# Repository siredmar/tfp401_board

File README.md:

tfp401_board
============

Hard- and Software for TFP401 Board to connect with 40 Pin RGB LCDs

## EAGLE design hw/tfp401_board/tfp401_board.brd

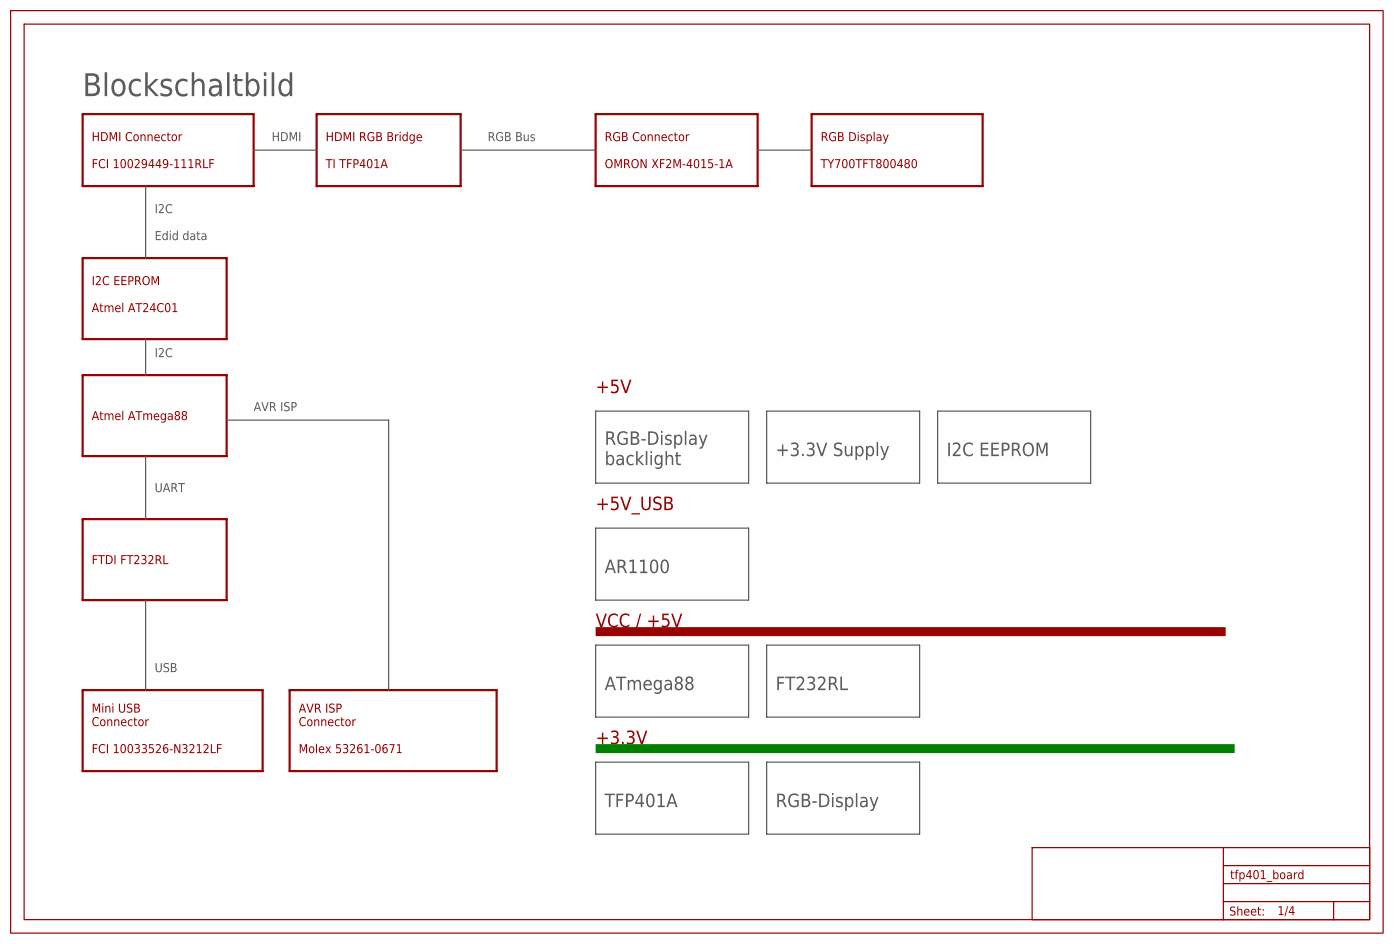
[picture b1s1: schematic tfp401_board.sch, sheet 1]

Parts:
U$15: FRAME_A3_LANDSCAPE; FRAME

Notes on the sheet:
HDMI Connector FCI 10029449-111RLF
RGB Display TY700TFT800480
Mini USB Connector FCI 10033526-N3212LF
AVR ISP Connector Molex 53261-0671
RGB Connector OMRON XF2M-4015-1A
HDMI RGB Bridge TI TFP401A
I2C EEPROM Atmel AT24C01
Atmel ATmega88
Edid data
RGB Bus
I2C
USB
AVR ISP
HDMI
Blockschaltbild
+3.3V
VCC / +5V
ATmega88
I2C EEPROM
FT232RL
TFP401A
FTDI FT232RL
UART
RGB-Display backlight
RGB-Display
+5V
AR1100
+5V_USB
+3.3V Supply

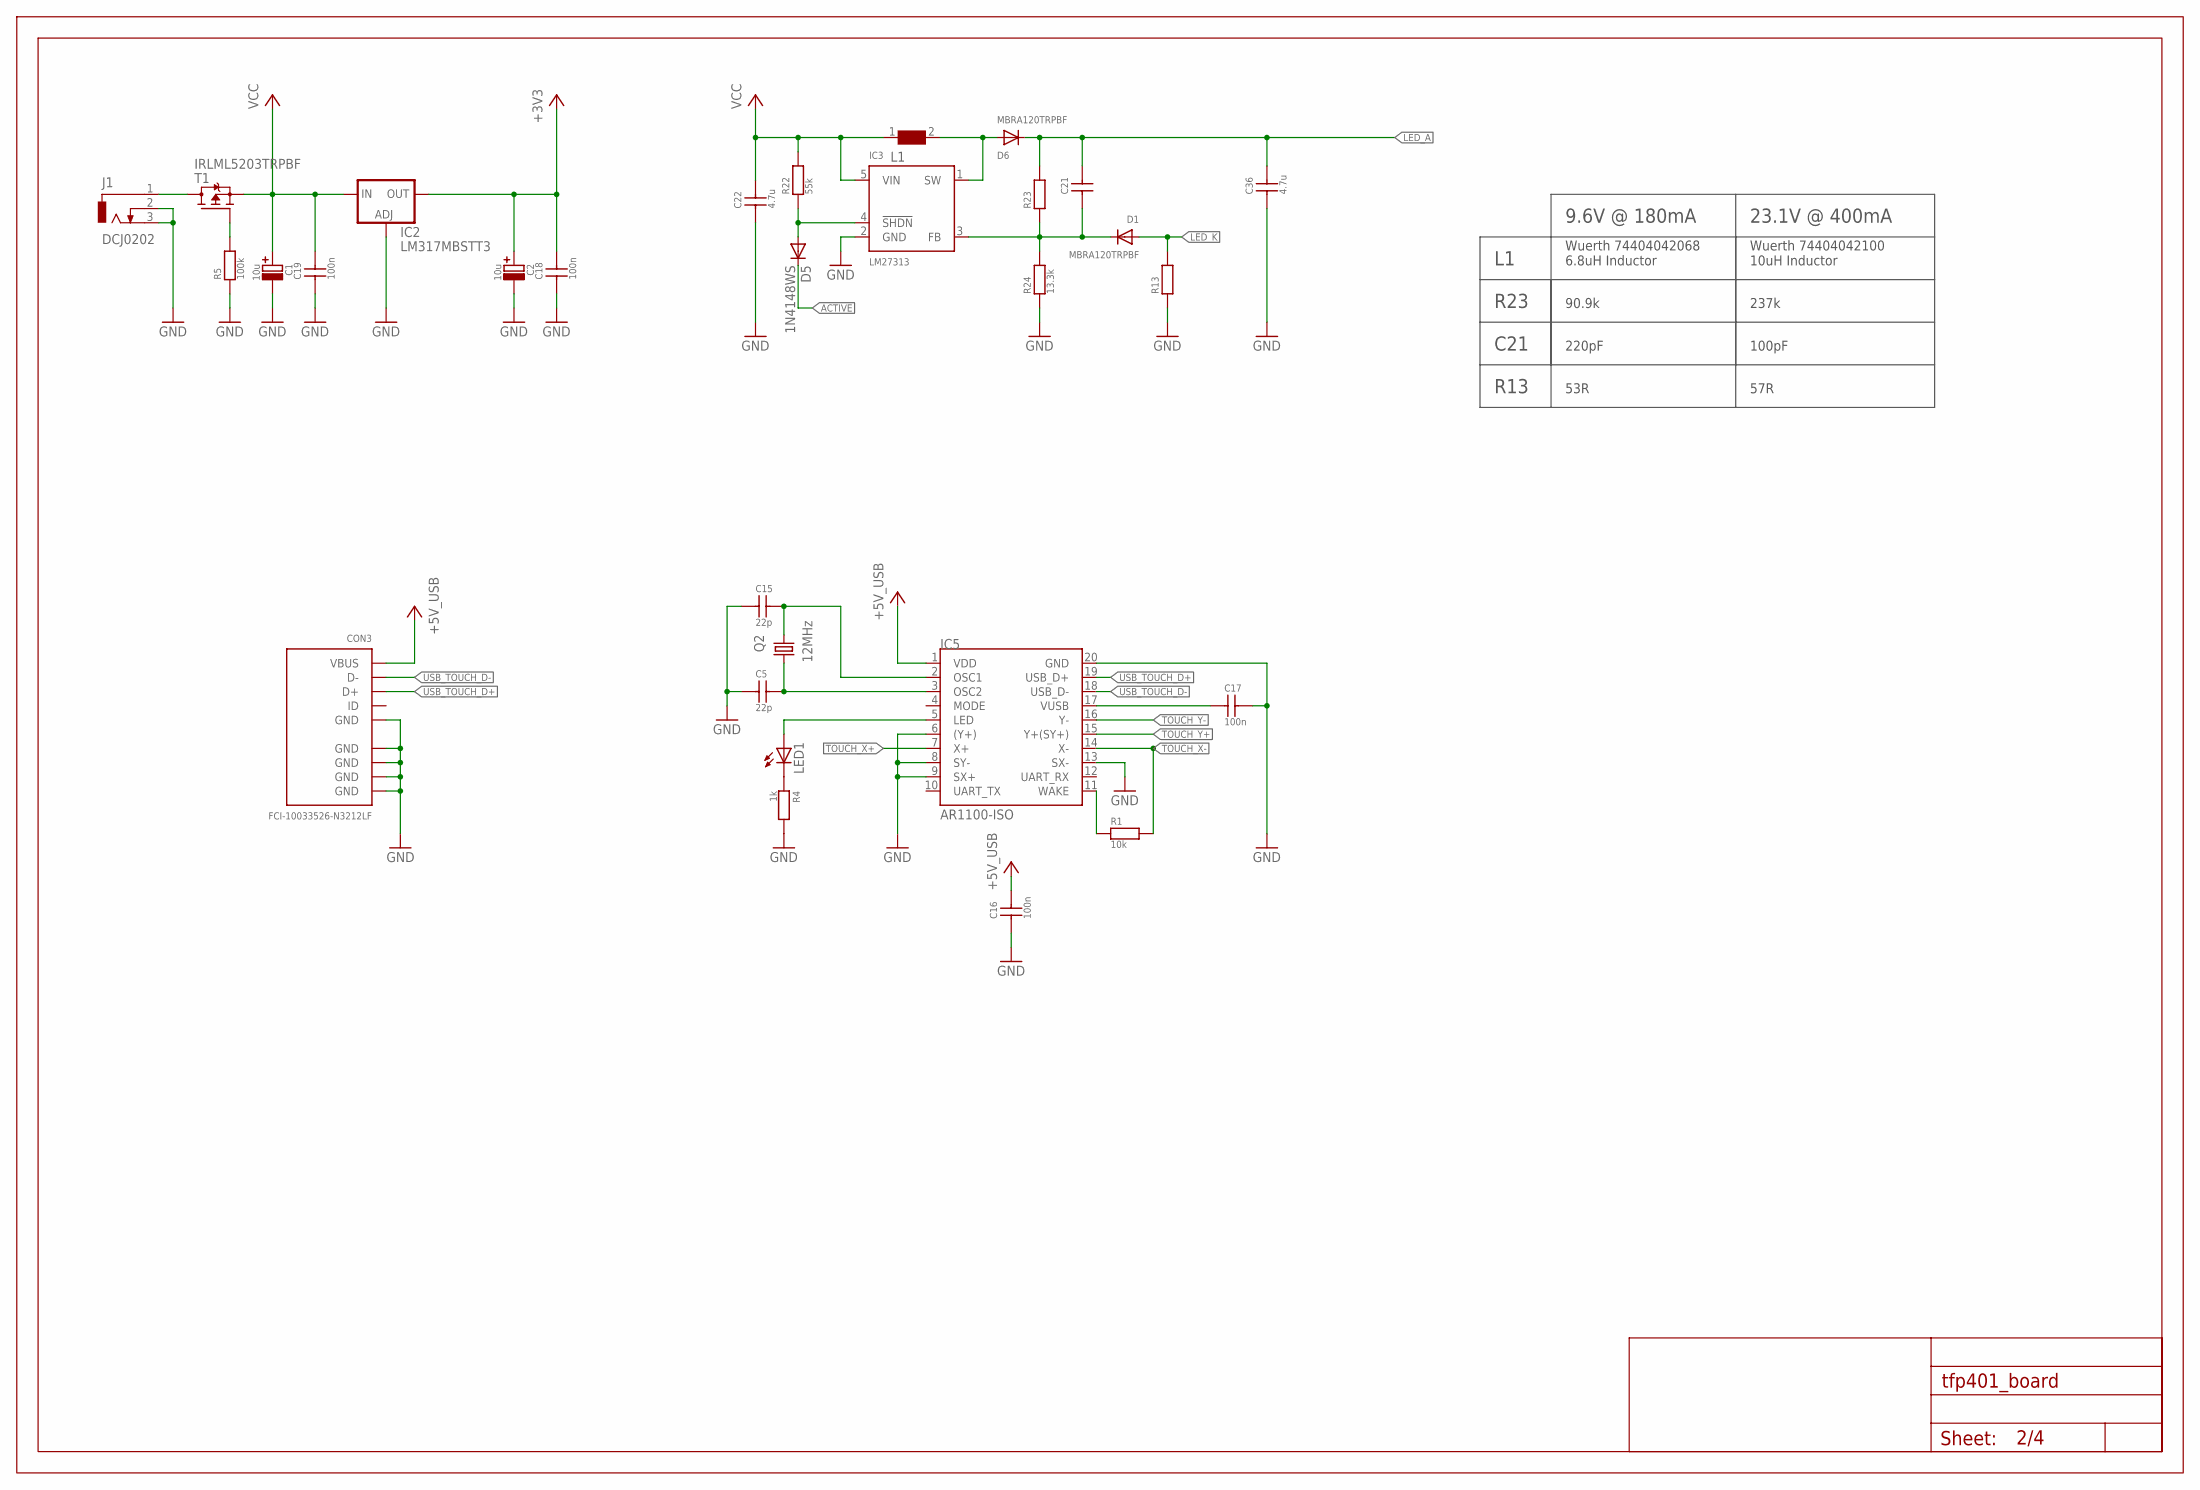
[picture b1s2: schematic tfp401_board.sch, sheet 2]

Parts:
C1, C2: 10u; C_POL_4X4MM
C5, C15: 22p; C0603
C16, C17, C18, C19: 100n; C0603
C21: C_SMD0603; C0603
C22, C36: 4.7u; C1206
CON3: FCI-10033526-N3212LF
D1, D6: MBRA120TRPBF; SMADIODE
D5: 1N4148WS; SOD323-W
IC2: LM317MBSTT3; SOT223
IC3: LM27313; SOT23-5
IC5: AR1100-ISO; SOIC20
J1: DCJ0202
L1: WE-LQS_4018
LED1: LEDCHIP-LED0805; CHIP-LED0805
Q2: 12MHz; HC49/USSM
R1: 10k; R0603
R4: 1k; R0603
R5: 100k; R0603
R13: R2512
R22: 55k; R0603
R23: R0603
R24: 13.3k; R0603
T1: IRLML5203TRPBF; SOT23
U$2: FRAME_A3_LANDSCAPE; FRAME

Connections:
+3V3: C2.+, C18.2, IC2.4 (OUT); also elsewhere on the board
+5V_USB: C16.2, CON3.1 (VBUS), IC5.1 (VDD)
ACTIVE: D5.C; also elsewhere on the board
GND: C1.-, C2.-, C5.1, C15.1, C16.1, C17.2, C18.1, C19.1, C22.1, C36.1, CON3.5 (GND), CON3.GND@1 (GND), CON3.GND@2 (GND), CON3.GND@3 (GND), CON3.GND@4 (GND), IC2.1 (ADJ), IC3.2 (GND), IC5.6 ((Y+)), IC5.8 (SY-), IC5.9 (SX+), IC5.13 (SX-), IC5.20 (GND), J1.2, J1.3, R4.2, R5.1, R13.1, R24.1; also elsewhere on the board
LED_A: C21.2, C36.2, D6.C, R23.2; also elsewhere on the board
LED_K: D1.A, R13.2; also elsewhere on the board
unnamed: R5.2, T1.1 (G)
unnamed: IC5.11 (WAKE), R1.1
unnamed: C17.1, IC5.17 (VUSB)
unnamed: LED1.C, R4.1
unnamed: C15.2, IC5.2 (OSC1), Q2.1
unnamed: J1.1, T1.3 (D)
unnamed: C5.2, IC5.3 (OSC2), Q2.2
unnamed: D6.A, IC3.1 (SW), L1.2
unnamed: D5.A, IC3.4 (!SHDN), R22.1
unnamed: IC5.5 (LED), LED1.A
unnamed: C21.1, D1.C, IC3.3 (FB), R23.1, R24.2
TOUCH_X+: IC5.7 (X+); also elsewhere on the board
TOUCH_X-: IC5.14 (X-), R1.2; also elsewhere on the board
TOUCH_Y+: IC5.15 (Y+(SY+)); also elsewhere on the board
TOUCH_Y-: IC5.16 (Y-); also elsewhere on the board
USB_TOUCH_D+: CON3.3 (D+), IC5.19 (USB_D+)
USB_TOUCH_D-: CON3.2 (D-), IC5.18 (USB_D-)
VCC: C1.+, C19.2, C22.2, IC2.3 (IN), IC3.5 (VIN), L1.1, R22.2, T1.2 (S); also elsewhere on the board

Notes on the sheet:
9.6V @ 180mA
23.1V @ 400mA
R23
Wuerth 74404042068 6.8uH Inductor
Wuerth 74404042100 10uH Inductor
C21
90.9k
237k
100pF
220pF
R13
57R
53R

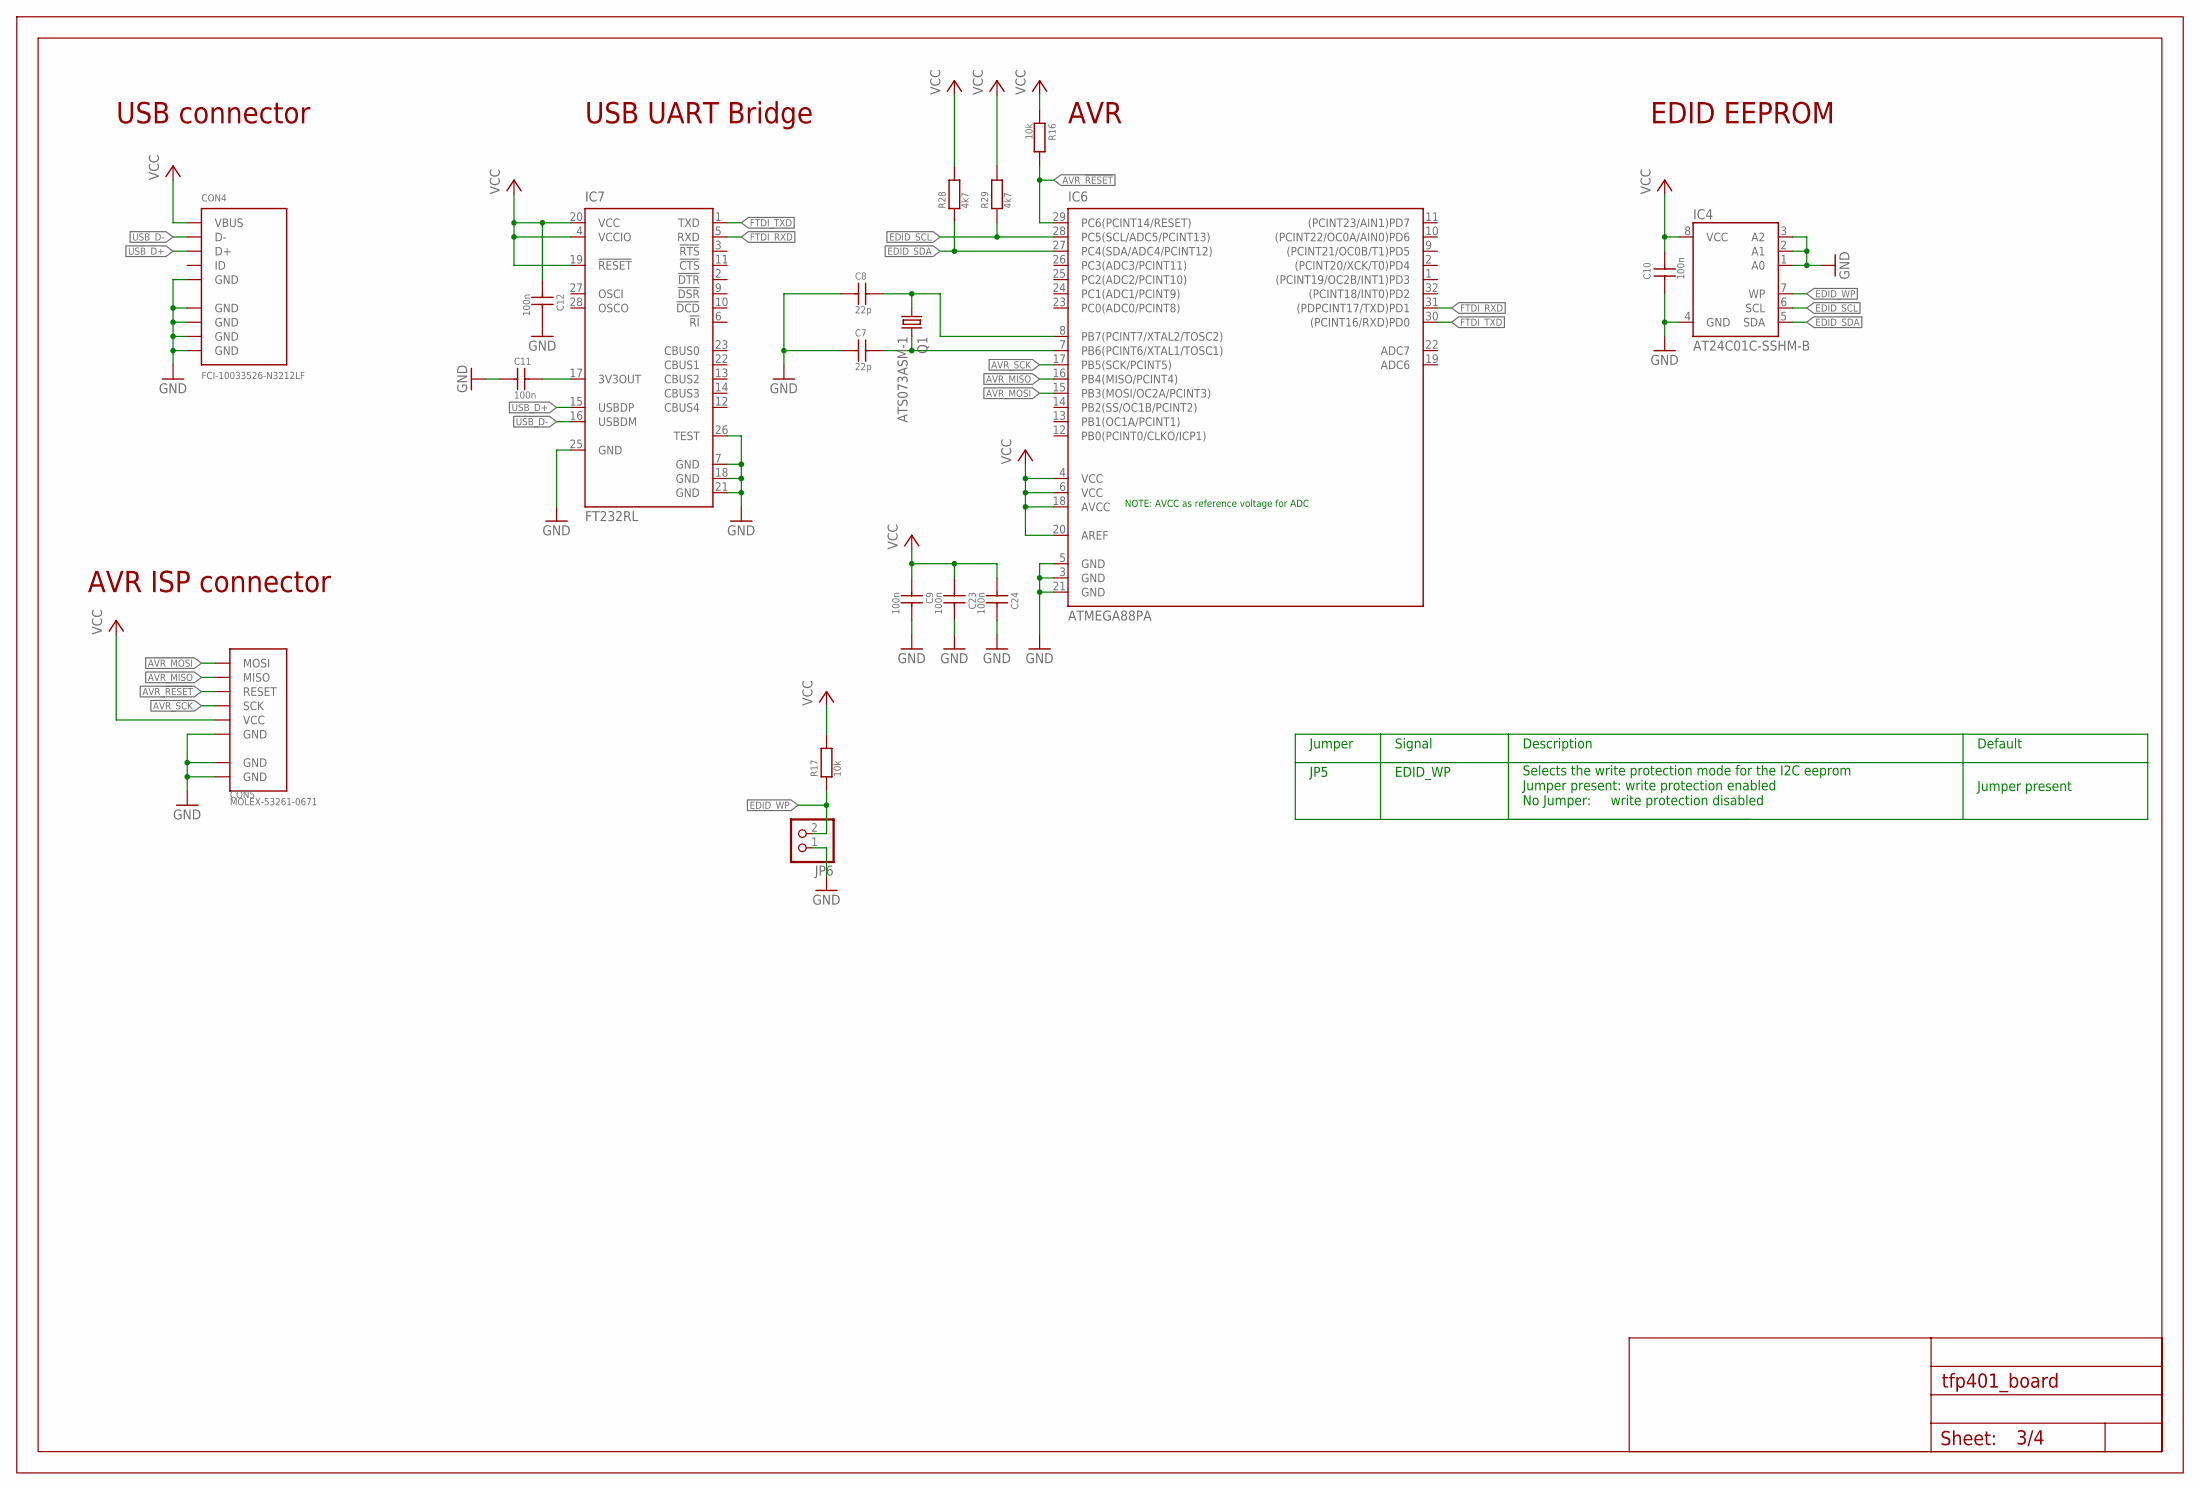
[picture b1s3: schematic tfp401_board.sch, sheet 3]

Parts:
C7, C8: 22p; C0603
C9, C10, C11, C12, C23, C24: 100n; C0603
CON4: FCI-10033526-N3212LF
CON5: MOLEX-53261-0671
IC4: AT24C01C-SSHM-B; SOIC8
IC6: ATMEGA88PA; TQFP32
IC7: FT232RL; SSOP28
JP6: PINHD-1X02_2.54-SMD-90°; 1X02SMD/90
Q1: ATS073ASM-1; HC49/USSM
R16, R17: 10k; R0603
R28, R29: 4k7; R0603
U$4: FRAME_A3_LANDSCAPE; FRAME

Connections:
AVR_!RESET: CON5.3 (RESET), IC6.29 (PC6(PCINT14/RESET)), R16.2
AVR_MISO: CON5.2 (MISO), IC6.16 (PB4(MISO/PCINT4))
AVR_MOSI: CON5.1 (MOSI), IC6.15 (PB3(MOSI/OC2A/PCINT3))
AVR_SCK: CON5.4 (SCK), IC6.17 (PB5(SCK/PCINT5))
AVR_XTAL1: C7.2, IC6.7 (PB6(PCINT6/XTAL1/TOSC1)), Q1.2
AVR_XTAL2: C8.2, IC6.8 (PB7(PCINT7/XTAL2/TOSC2)), Q1.1
EDID_SCL: IC4.6 (SCL), IC6.28 (PC5(SCL/ADC5/PCINT13)), R29.1; also elsewhere on the board
EDID_SDA: IC4.5 (SDA), IC6.27 (PC4(SDA/ADC4/PCINT12)), R28.1; also elsewhere on the board
EDID_WP: IC4.7 (WP), JP6.2, R17.1
FTDI_3V3OUT: C11.2, IC7.17 (3V3OUT)
FTDI_RXD: IC6.31 ((PDPCINT17/TXD)PD1), IC7.5 (RXD)
FTDI_TXD: IC6.30 ((PCINT16/RXD)PD0), IC7.1 (TXD)
GND: C7.1, C8.1, C9.2, C10.1, C11.1, C12.2, C23.2, C24.2, CON4.5 (GND), CON4.GND@1 (GND), CON4.GND@2 (GND), CON4.GND@3 (GND), CON4.GND@4 (GND), CON5.6 (GND), CON5.GND@1 (GND), CON5.GND@2 (GND), IC4.1 (A0), IC4.2 (A1), IC4.3 (A2), IC4.4 (GND), IC6.3 (GND), IC6.5 (GND), IC6.21 (GND), IC7.7 (GND), IC7.18 (GND), IC7.21 (GND), IC7.25 (GND), IC7.26 (TEST), JP6.1; also elsewhere on the board
USB_D+: CON4.3 (D+), IC7.15 (USBDP)
USB_D-: CON4.2 (D-), IC7.16 (USBDM)
VCC: C9.1, C10.2, C12.1, C23.1, C24.1, CON4.1 (VBUS), CON5.5 (VCC), IC4.8 (VCC), IC6.4 (VCC), IC6.6 (VCC), IC6.18 (AVCC), IC6.20 (AREF), IC7.4 (VCCIO), IC7.19 (!RESET), IC7.20 (VCC), R16.1, R17.2, R28.2, R29.2; also elsewhere on the board

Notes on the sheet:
NOTE: AVCC as reference voltage for ADC
JP5
Jumper
Description
Signal
EDID_WP
Selects the write protection mode for the I2C eeprom Jumper present: write protection enabled No Jumper: write protection disabled
Default
Jumper present
EDID EEPROM
AVR
USB UART Bridge
AVR ISP connector
USB connector

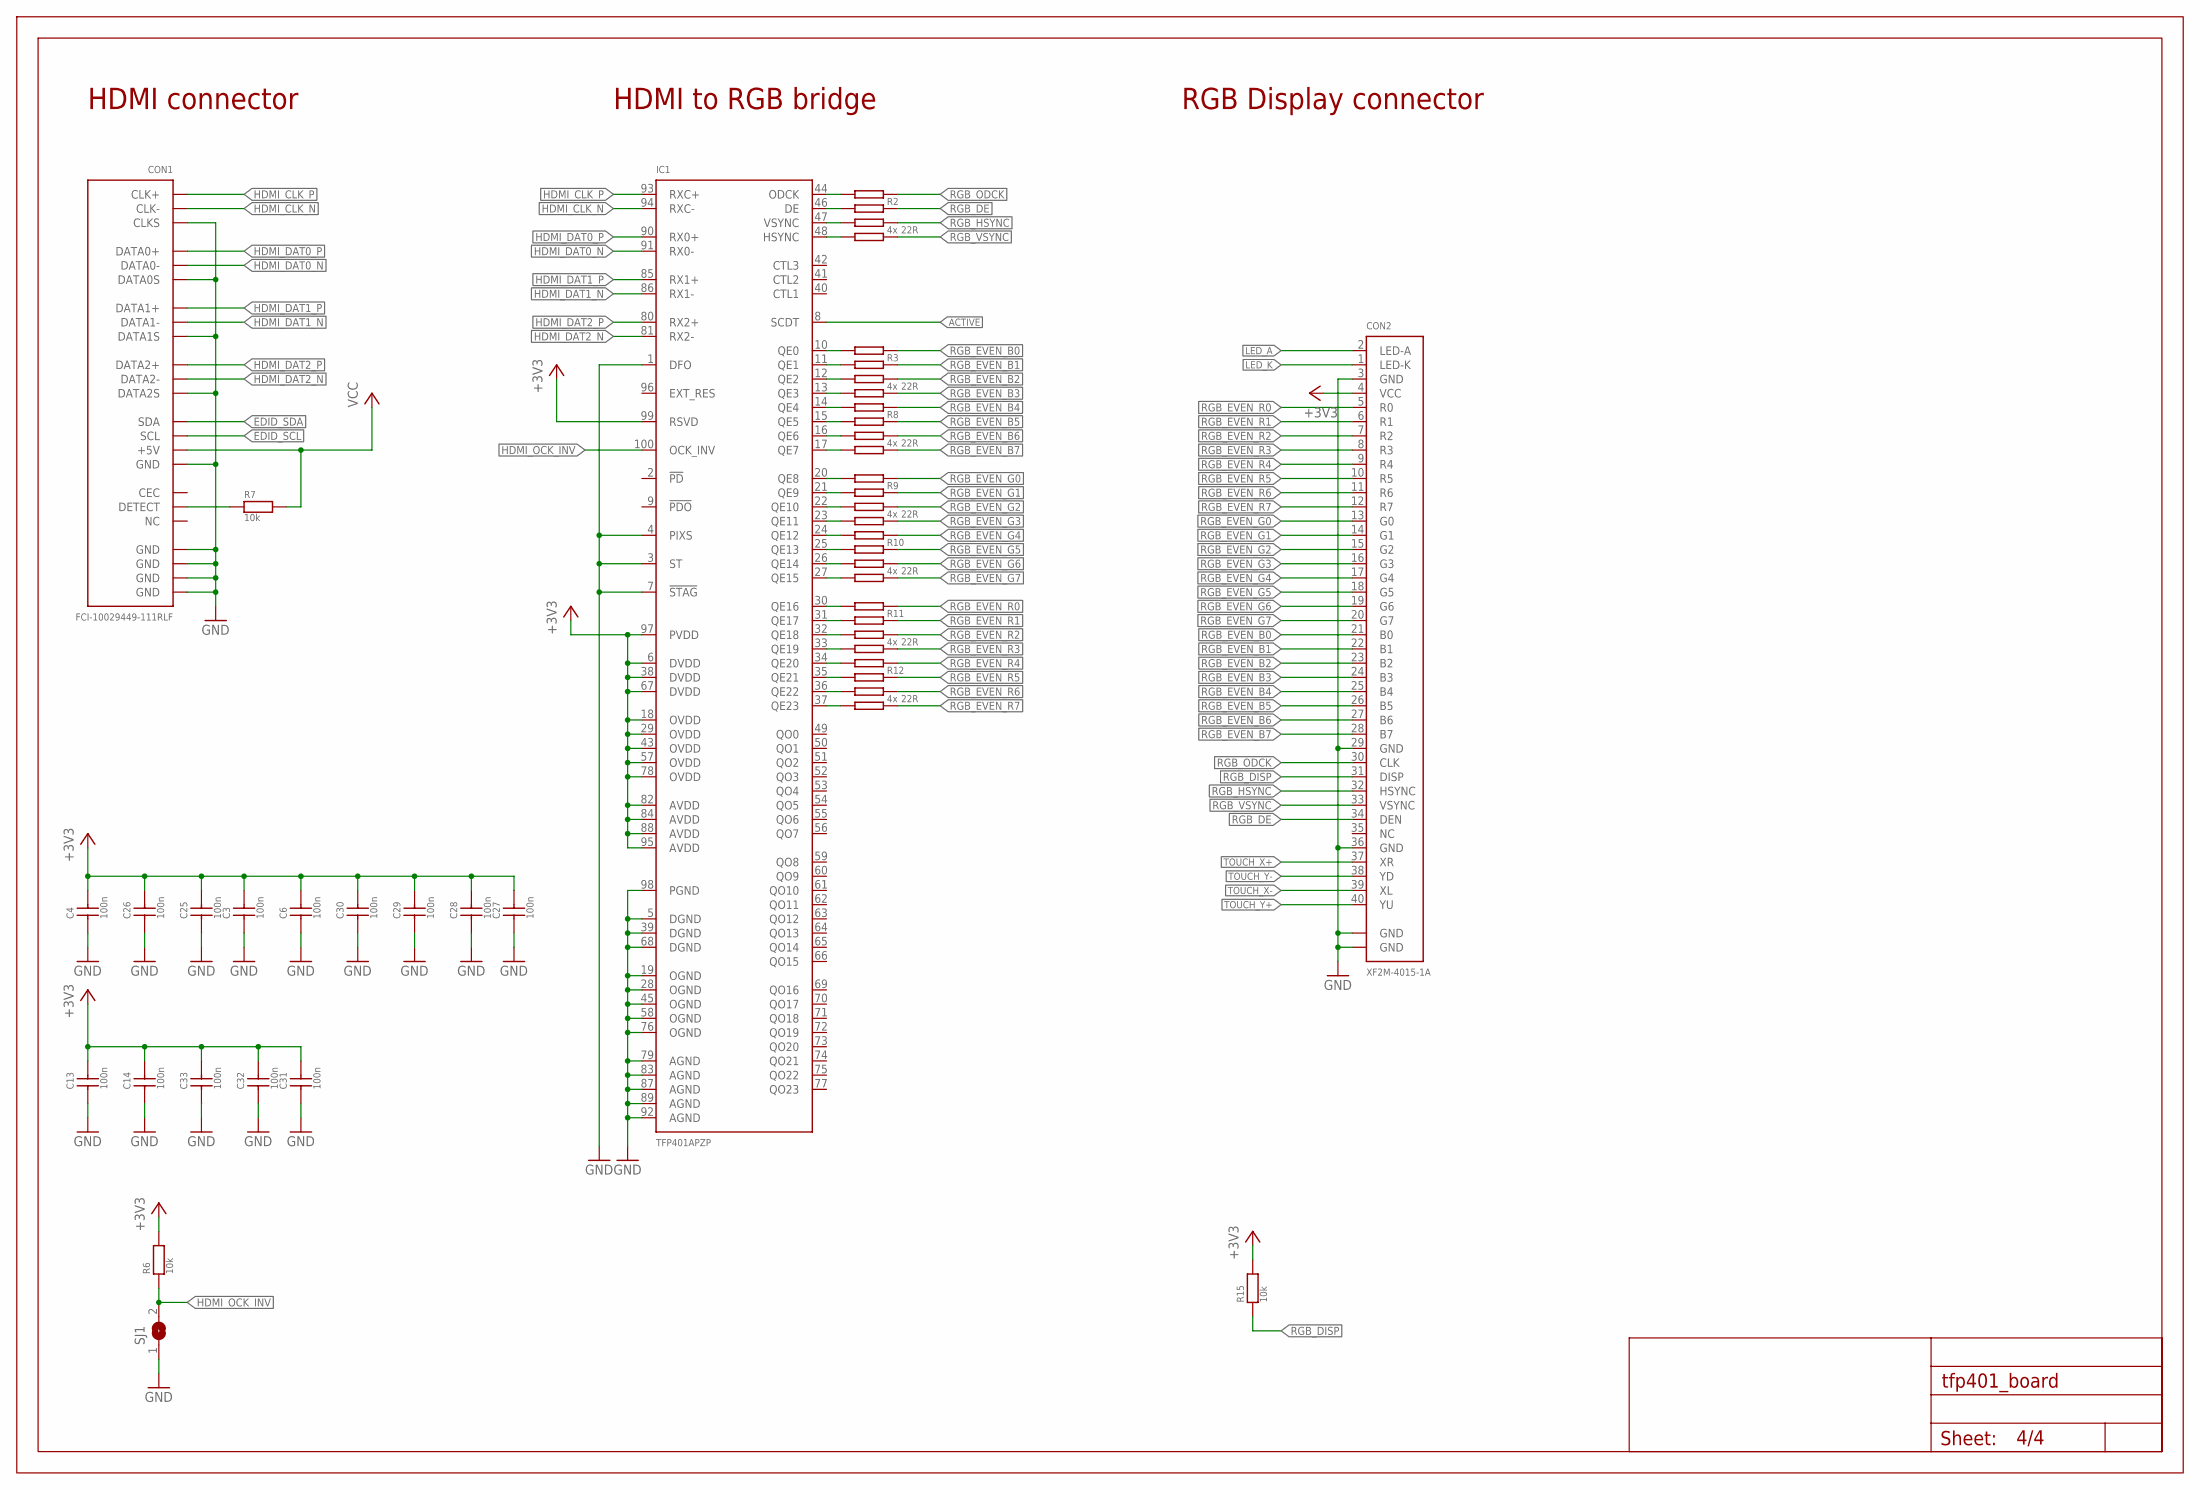
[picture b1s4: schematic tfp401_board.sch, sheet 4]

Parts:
C3, C4, C6, C13, C14, C25, C26, C27, C28, C29, C30, C31, C32, C33: 100n; C0603
CON1: FCI-10029449-111RLF
CON2: XF2M-4015-1A
IC1: TFP401APZP; HTQFP-100
R2, R3, R8, R9, R10, R11, R12: 22R; R-ARRAY-4X0603
R6, R7, R15: 10k; R0603
SJ1: SJ
U$1: FRAME_A3_LANDSCAPE; FRAME

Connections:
+3V3: C3.2, C4.2, C6.2, C13.2, C14.2, C25.2, C26.2, C27.2, C28.2, C29.2, C30.2, C31.2, C32.2, C33.2, CON2.4 (VCC), IC1.6 (DVDD), IC1.18 (OVDD), IC1.29 (OVDD), IC1.38 (DVDD), IC1.43 (OVDD), IC1.57 (OVDD), IC1.67 (DVDD), IC1.78 (OVDD), IC1.82 (AVDD), IC1.84 (AVDD), IC1.88 (AVDD), IC1.95 (AVDD), IC1.97 (PVDD), IC1.99 (RSVD), R6.2, R15.2; also elsewhere on the board
ACTIVE: IC1.8 (SCDT); also elsewhere on the board
EDID_SCL: CON1.15 (SCL); also elsewhere on the board
EDID_SDA: CON1.16 (SDA); also elsewhere on the board
GND: C3.1, C4.1, C6.1, C13.1, C14.1, C25.1, C26.1, C27.1, C28.1, C29.1, C30.1, C31.1, C32.1, C33.1, CON1.2 (DATA2S), CON1.5 (DATA1S), CON1.8 (DATA0S), CON1.11 (CLKS), CON1.17 (GND), CON1.GND@1 (GND), CON1.GND@2 (GND), CON1.GND@3 (GND), CON1.GND@4 (GND), CON2.3 (GND), CON2.29 (GND), CON2.36 (GND), CON2.GND@1 (GND), CON2.GND@2 (GND), IC1.1 (DFO), IC1.3 (ST), IC1.4 (PIXS), IC1.5 (DGND), IC1.7 (!STAG), IC1.19 (OGND), IC1.28 (OGND), IC1.39 (DGND), IC1.45 (OGND), IC1.58 (OGND), IC1.68 (DGND), IC1.76 (OGND), IC1.79 (AGND), IC1.83 (AGND), IC1.87 (AGND), IC1.89 (AGND), IC1.92 (AGND), IC1.98 (PGND), SJ1.1; also elsewhere on the board
HDMI_CLK_N: CON1.12 (CLK-), IC1.94 (RXC-)
HDMI_CLK_P: CON1.10 (CLK+), IC1.93 (RXC+)
HDMI_DAT0_N: CON1.9 (DATA0-), IC1.91 (RX0-)
HDMI_DAT0_P: CON1.7 (DATA0+), IC1.90 (RX0+)
HDMI_DAT1_N: CON1.6 (DATA1-), IC1.86 (RX1-)
HDMI_DAT1_P: CON1.4 (DATA1+), IC1.85 (RX1+)
HDMI_DAT2_N: CON1.3 (DATA2-), IC1.81 (RX2-)
HDMI_DAT2_P: CON1.1 (DATA2+), IC1.80 (RX2+)
HDMI_OCK_INV: IC1.100 (OCK_INV), R6.1, SJ1.2
INT_RGB_DE: IC1.46 (DE), R2.3M
INT_RGB_EVEN_B0: IC1.10 (QE0), R3.4M
INT_RGB_EVEN_B1: IC1.11 (QE1), R3.3M
INT_RGB_EVEN_B2: IC1.12 (QE2), R3.2M
INT_RGB_EVEN_B3: IC1.13 (QE3), R3.1M
INT_RGB_EVEN_B4: IC1.14 (QE4), R8.4M
INT_RGB_EVEN_B5: IC1.15 (QE5), R8.3M
INT_RGB_EVEN_B6: IC1.16 (QE6), R8.2M
INT_RGB_EVEN_B7: IC1.17 (QE7), R8.1M
INT_RGB_EVEN_G0: IC1.20 (QE8), R9.4M
INT_RGB_EVEN_G1: IC1.21 (QE9), R9.3M
INT_RGB_EVEN_G2: IC1.22 (QE10), R9.2M
INT_RGB_EVEN_G3: IC1.23 (QE11), R9.1M
INT_RGB_EVEN_G4: IC1.24 (QE12), R10.4M
INT_RGB_EVEN_G5: IC1.25 (QE13), R10.3M
INT_RGB_EVEN_G6: IC1.26 (QE14), R10.2M
INT_RGB_EVEN_G7: IC1.27 (QE15), R10.1M
INT_RGB_EVEN_R0: IC1.30 (QE16), R11.4M
INT_RGB_EVEN_R1: IC1.31 (QE17), R11.3M
INT_RGB_EVEN_R2: IC1.32 (QE18), R11.2M
INT_RGB_EVEN_R3: IC1.33 (QE19), R11.1M
INT_RGB_EVEN_R4: IC1.34 (QE20), R12.4M
INT_RGB_EVEN_R5: IC1.35 (QE21), R12.3M
INT_RGB_EVEN_R6: IC1.36 (QE22), R12.2M
INT_RGB_EVEN_R7: IC1.37 (QE23), R12.1M
INT_RGB_HSYNC: IC1.47 (VSYNC), R2.2M
INT_RGB_ODCK: IC1.44 (ODCK), R2.4M
INT_RGB_VSYNC: IC1.48 (HSYNC), R2.1M
LED_A: CON2.2 (LED-A); also elsewhere on the board
LED_K: CON2.1 (LED-K); also elsewhere on the board
unnamed: CON1.19 (DETECT), R7.1
RGB_DE: CON2.34 (DEN), R2.3P
RGB_DISP: CON2.31 (DISP), R15.1
RGB_EVEN_B0: CON2.21 (B0), R3.4P
RGB_EVEN_B1: CON2.22 (B1), R3.3P
RGB_EVEN_B2: CON2.23 (B2), R3.2P
RGB_EVEN_B3: CON2.24 (B3), R3.1P
RGB_EVEN_B4: CON2.25 (B4), R8.4P
RGB_EVEN_B5: CON2.26 (B5), R8.3P
RGB_EVEN_B6: CON2.27 (B6), R8.2P
RGB_EVEN_B7: CON2.28 (B7), R8.1P
RGB_EVEN_G0: CON2.13 (G0), R9.4P
RGB_EVEN_G1: CON2.14 (G1), R9.3P
RGB_EVEN_G2: CON2.15 (G2), R9.2P
RGB_EVEN_G3: CON2.16 (G3), R9.1P
RGB_EVEN_G4: CON2.17 (G4), R10.4P
RGB_EVEN_G5: CON2.18 (G5), R10.3P
RGB_EVEN_G6: CON2.19 (G6), R10.2P
RGB_EVEN_G7: CON2.20 (G7), R10.1P
RGB_EVEN_R0: CON2.5 (R0), R11.4P
RGB_EVEN_R1: CON2.6 (R1), R11.3P
RGB_EVEN_R2: CON2.7 (R2), R11.2P
RGB_EVEN_R3: CON2.8 (R3), R11.1P
RGB_EVEN_R4: CON2.9 (R4), R12.4P
RGB_EVEN_R5: CON2.10 (R5), R12.3P
RGB_EVEN_R6: CON2.11 (R6), R12.2P
RGB_EVEN_R7: CON2.12 (R7), R12.1P
RGB_HSYNC: CON2.32 (HSYNC), R2.2P
RGB_ODCK: CON2.30 (CLK), R2.4P
RGB_VSYNC: CON2.33 (VSYNC), R2.1P
TOUCH_X+: CON2.37 (XR); also elsewhere on the board
TOUCH_X-: CON2.39 (XL); also elsewhere on the board
TOUCH_Y+: CON2.40 (YU); also elsewhere on the board
TOUCH_Y-: CON2.38 (YD); also elsewhere on the board
VCC: CON1.18 (+5V), R7.2; also elsewhere on the board

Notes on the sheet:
HDMI connector
HDMI to RGB bridge
RGB Display connector

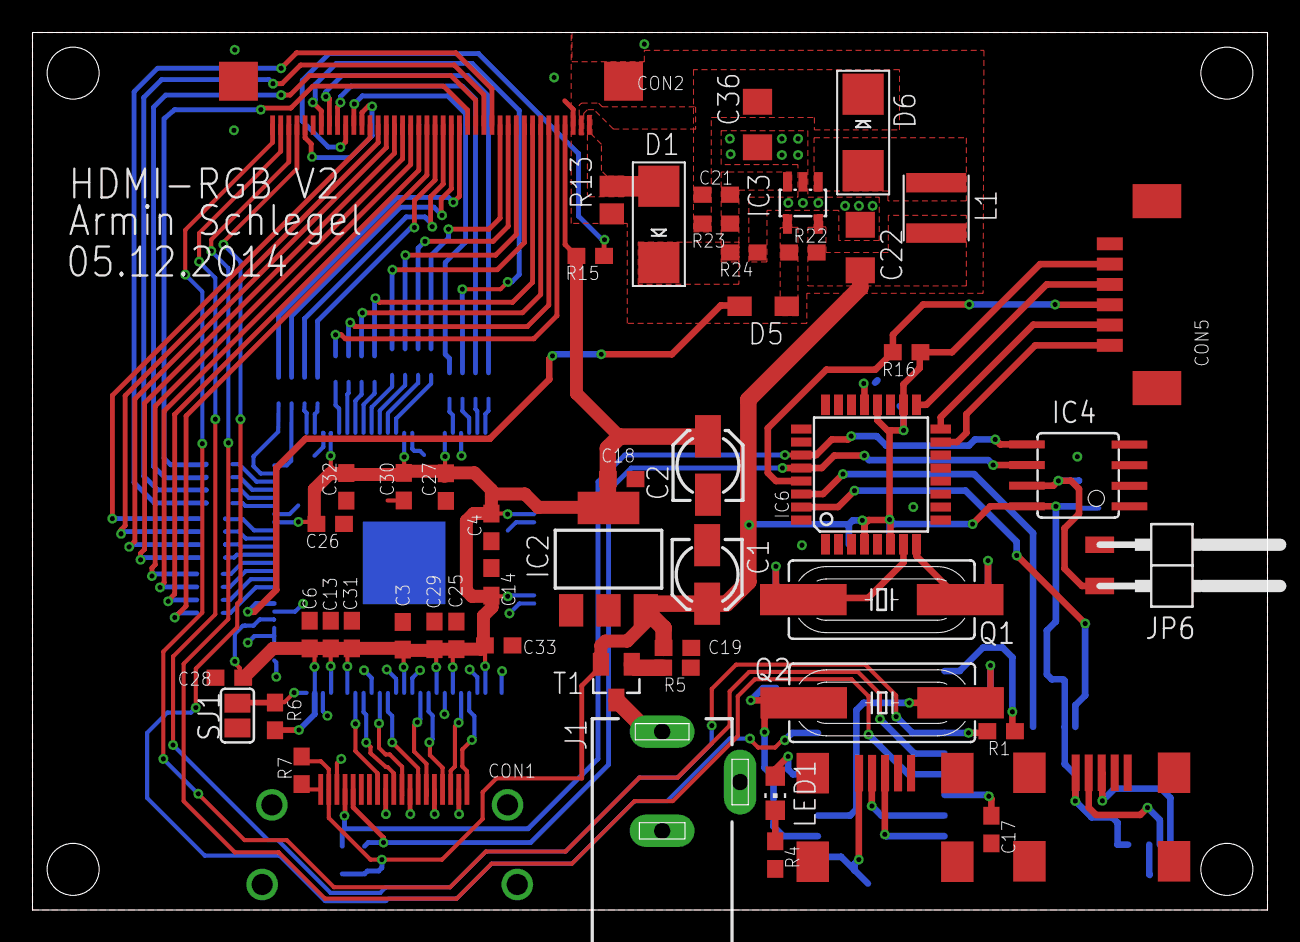
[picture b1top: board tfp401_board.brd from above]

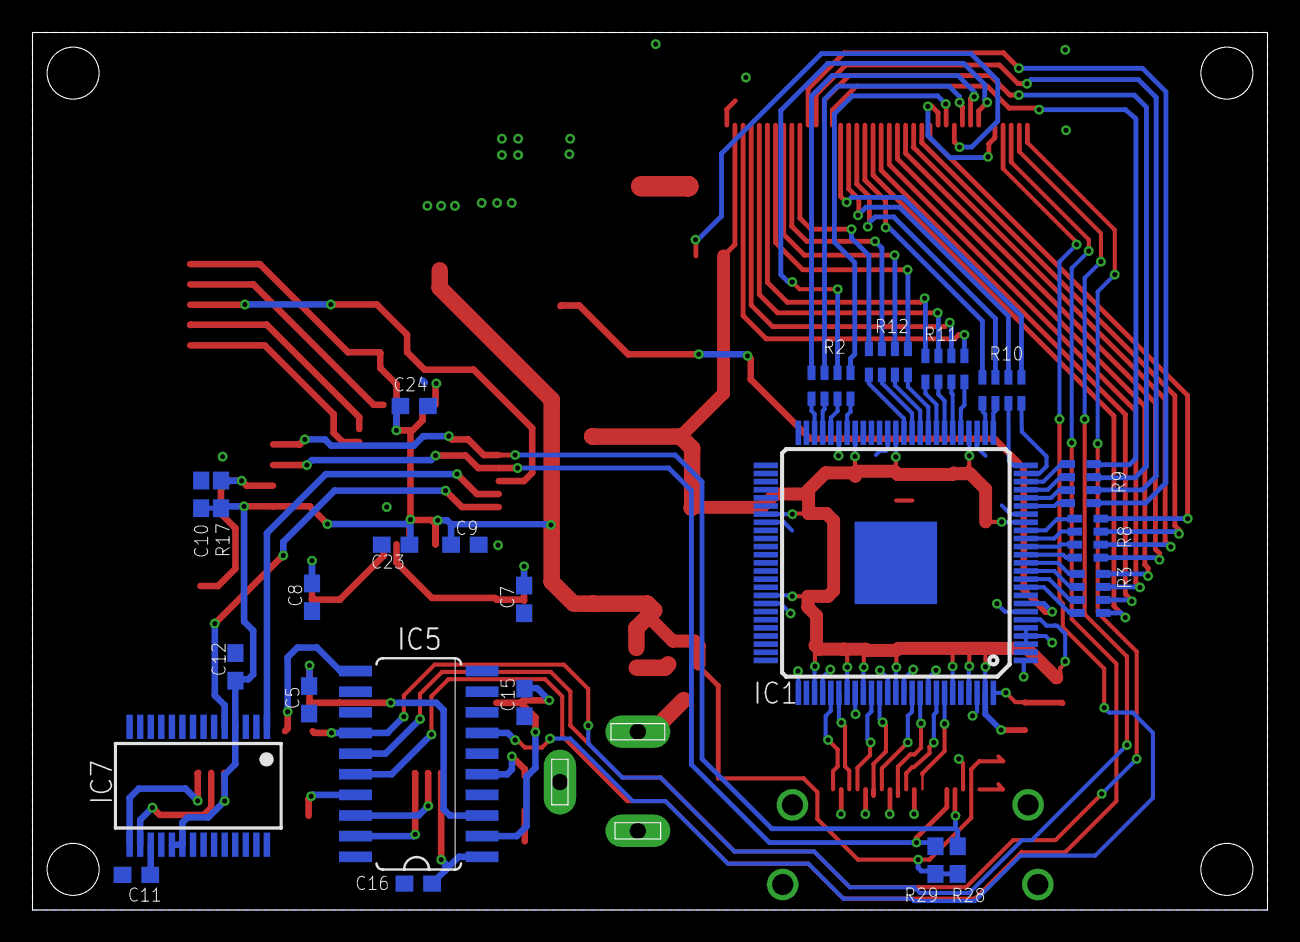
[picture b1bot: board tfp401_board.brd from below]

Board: 2 copper layers, 76.0 x 54.0 mm, 81 parts (24 on the bottom side), 105 nets.

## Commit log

2014-12-05 layout v1 done

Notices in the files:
parts and their libraries:
EagleLibrary_Wuerth_Elektronik_eiSos_V6_: Copyright: Würth Elektronik
